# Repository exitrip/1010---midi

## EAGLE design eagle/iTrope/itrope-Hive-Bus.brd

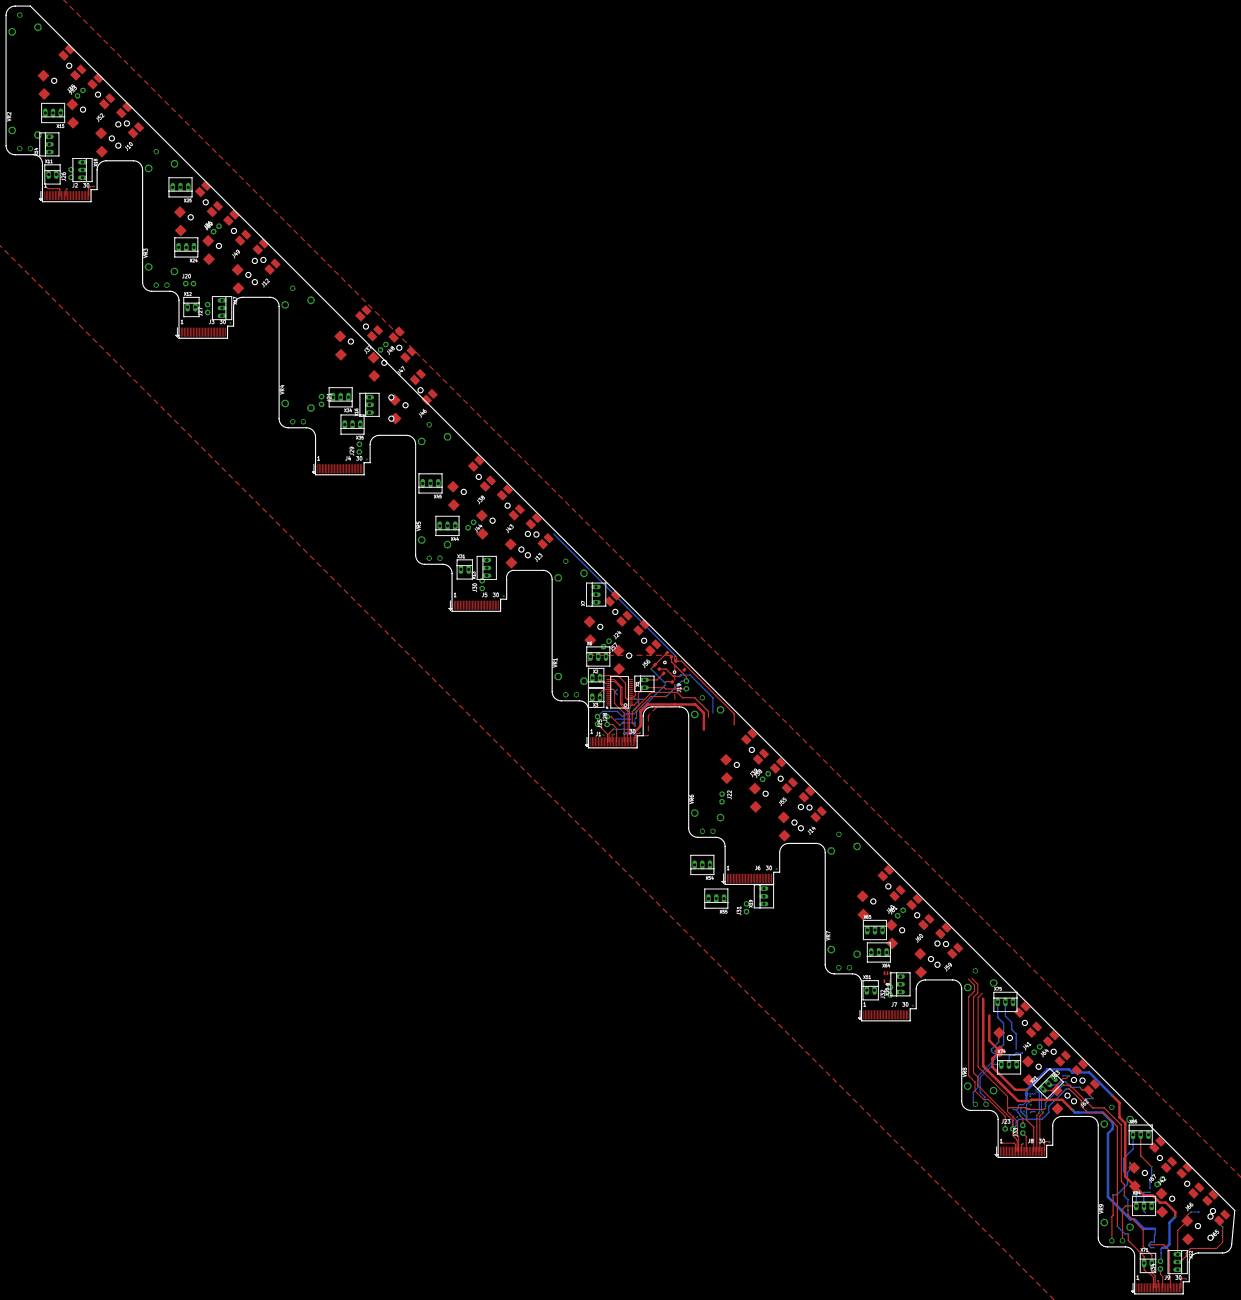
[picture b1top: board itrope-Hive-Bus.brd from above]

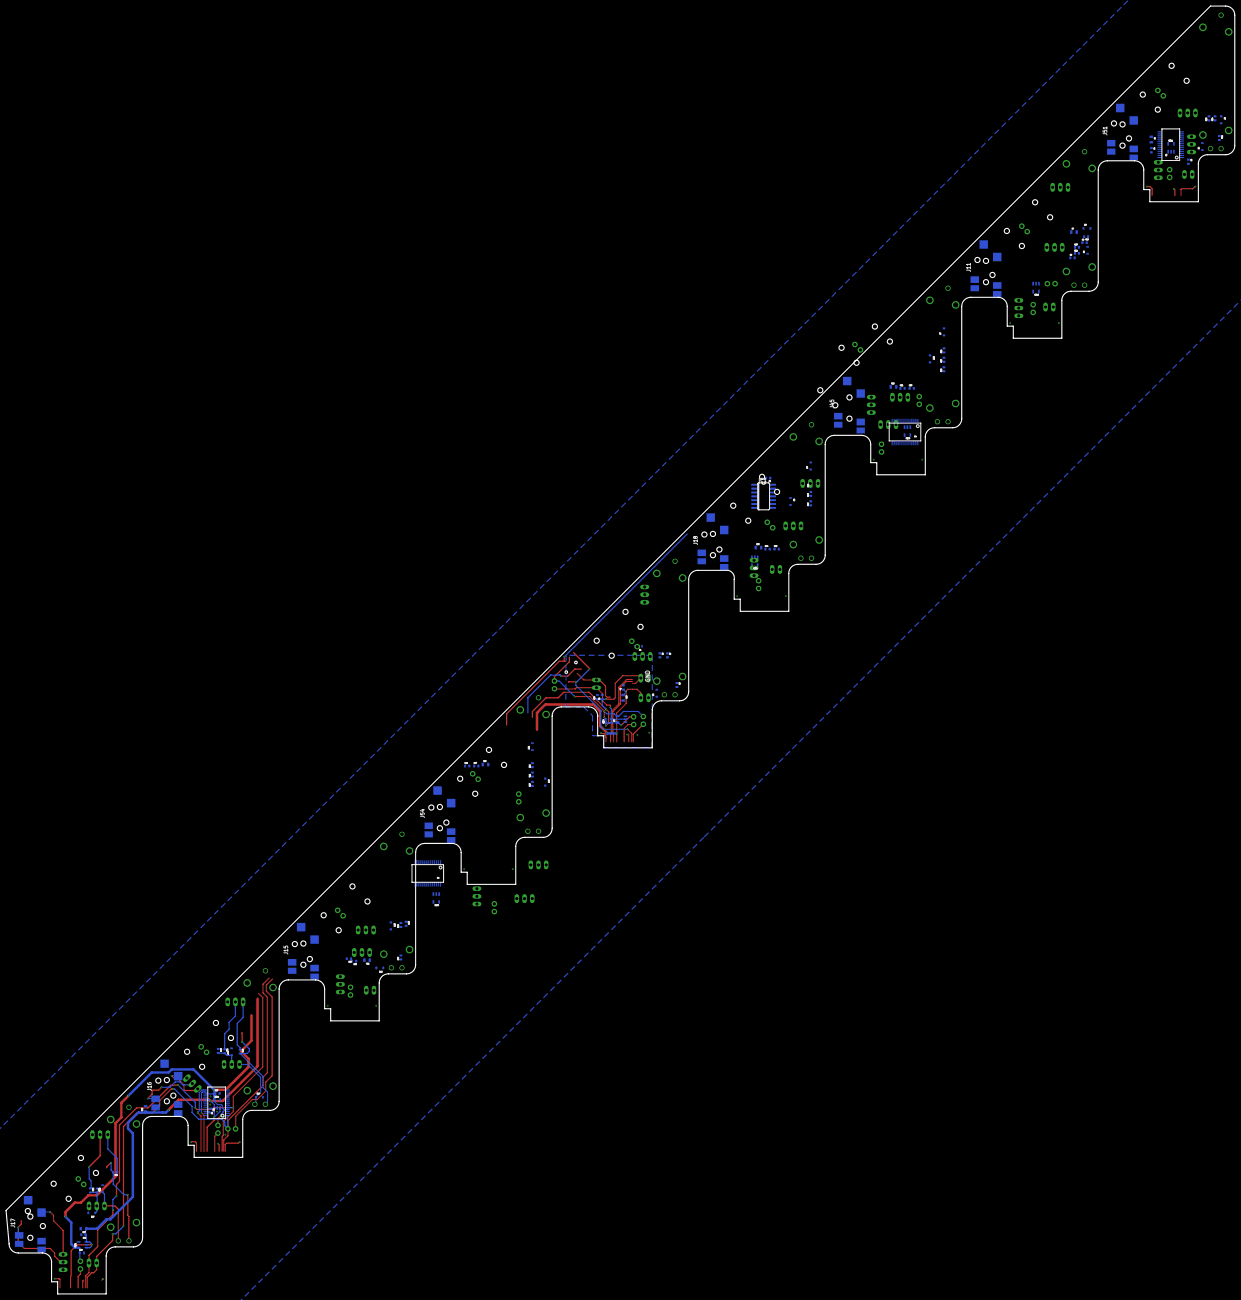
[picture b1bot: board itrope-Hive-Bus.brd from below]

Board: 2 copper layers, 405.0 x 424.5 mm, 201 parts (96 on the bottom side), 105 nets.

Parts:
C1, C2, C3, C4, C5, C8, C9, C10, C11, C13, C14, C17, C18, C19, C20, C23, C24, C25, C26, C28: 0.1uF; CAP-0603
C6, C7, C12, C15, C16, C21, C22, C27, C30: 10uF; CAP-0805
D1, D2, D3, D4, D5, D6, D7, D8, D9, D10, D11, D12, D13, D14, D15, D16, D17, D19: SOD-323
IC1: 74ALS08D; SO14
J1, J2, J3, J4, J5, J6, J7, J8, J9: ITRIP-V1; 30PINEDGE+ITRIP
J10, J11, J12, J13, J14, J15, J16, J17, J18, J24, J35, J36, J37, J38, J39, J40, J41, J42, J43, J45, J46, J47, J49, J51, J52, J54, J55, J56, J59, J60, J62, J63, J65, J66: CUI-SJ-4351
J19, J20, J21, J22, J23, J25, J26, J27, J28, J29, J30, J31, J32, J33, J34, J44, J48, J50, J53, J57, J58, J61, J64, J67: H02-PTH
R5, R7, R12, R14, R19, R21, R26, R28, R33, R35, R40, R42, R47, R49, R54, R56, R61, R63: 33k; C0402
R6, R13, R20, R27, R34, R41, R48, R55, R62: 10k; C0402
SW1: SWITCH-CK-AYZ0203
U1, U2, U4, U6, U8: FT232RL-BASICSSOP; SSOP28DB
U5: 74AHC1G125; SOT23-5
U$11, U$19, U$26, U$33, U$40, U$47, U$54, U$61: V_REG_SOT23-5_EN; SOT23-5
U$39: 74LVC1T45; SC70-6
VR1, VR2, VR3, VR4, VR5, VR6, VR7, VR8, VR9: 10K; POT-SLIDE-30MM
X1, X2, X3, X11, X12, X31, X51, X71: 22-23-2021
X6, X7, X13, X14, X15, X16, X17, X18, X19, X20, X21, X22, X24, X25, X34, X35, X44, X45, X54, X55, X64, X65, X74, X75, X84, X85: 22-23-2031

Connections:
1D+: J2.P$27, U2.15
1D-: J2.P$25, U2.16
2D+: J4.P$27, U4.15
2D-: J4.P$25, U4.16
3D+: J6.P$27, U6.15
3D-: J6.P$25, U6.16
4D+: J8.P$27, U8.15
4D-: J8.P$25, U8.16
5V: C1.1, C4.1, C6.1, C7.1, C9.1, C10.1, C12.1, C14.1, C15.1, C16.1, C18.1, C20.1, C21.1, C22.1, C24.1, C26.1, C27.1, C30.1, J1.P$23, J2.P$23, J3.P$23, J4.P$23, J5.P$23, J6.P$23, J7.P$23, J8.P$23, J9.P$23, U1.20, U2.20, U4.20, U6.20, U8.20, U$11.1, U$11.3, U$19.1, U$19.3, U$26.1, U$26.3, U$33.1, U$33.3, U$40.1, U$40.3, U$47.1, U$47.3, U$54.1, U$54.3, U$61.1, U$61.3, X3.1
+3V3: C2.1, C3.1, C5.1, C8.1, C11.1, C13.1, C17.1, C19.1, C23.1, C25.1, C28.1, IC1.14, J24.5, J25.2, J26.2, J27.2, J29.2, J30.2, J31.2, J32.2, J33.2, J34.2, J35.5, J36.5, J37.5, J38.5, J39.5, J40.5, J41.5, J42.5, U1.4, U1.17, U2.4, U2.17, U4.4, U4.17, U5.5, U6.4, U6.17, U8.4, U8.17, U$11.5, U$19.5, U$26.5, U$33.5, U$39.1, U$39.5, U$39.6, U$40.5, U$47.5, U$54.5, U$61.5, X2.1
COD+: J1.P$27, U1.15
COD-: J1.P$25, U1.16
GND: C1.2, C2.2, C3.2, C4.2, C5.2, C6.2, C7.2, C8.2, C9.2, C10.2, C11.2, C12.2, C13.2, C14.2, C15.2, C16.2, C17.2, C18.2, C19.2, C20.2, C21.2, C22.2, C23.2, C24.2, C25.2, C26.2, C27.2, C28.2, C30.2, D1.2, D2.2, D3.2, D4.2, D5.2, D6.2, D7.2, D8.2, D9.2, D10.2, D11.2, D12.2, D13.2, D14.2, D15.2, D16.2, D17.2, D19.2, IC1.7, J1.P$1, J1.P$11, J1.P$15, J1.P$16, J1.P$29, J1.P$30, J2.P$1, J2.P$11, J2.P$15, J2.P$16, J2.P$29, J2.P$30, J3.P$1, J3.P$11, J3.P$15, J3.P$16, J3.P$29, J3.P$30, J4.P$1, J4.P$11, J4.P$15, J4.P$16, J4.P$29, J4.P$30, J5.P$1, J5.P$11, J5.P$15, J5.P$16, J5.P$29, J5.P$30, J6.P$1, J6.P$11, J6.P$15, J6.P$16, J6.P$29, J6.P$30, J7.P$1, J7.P$11, J7.P$15, J7.P$16, J7.P$29, J7.P$30, J8.P$1, J8.P$11, J8.P$15, J8.P$16, J8.P$29, J8.P$30, J9.P$1, J9.P$11, J9.P$15, J9.P$16, J9.P$29, J9.P$30, J10.1, J10.4, J11.1, J11.4, J12.1, J12.4, J13.1, J13.4, J14.1, J14.4, J15.1, J15.4, J16.1, J16.4, J17.1, J17.4, J18.1, J18.4, J24.1, J24.4, J35.1, J35.4, J36.1, J36.4, J37.1, J37.4, J38.1, J38.4, J39.1, J39.4, J40.1, J40.4, J41.1, J41.4, J42.1, J42.4, J43.1, J43.4, J44.2, J45.1, J45.4, J46.1, J46.4, J47.1, J47.4, J48.2, J49.1, J49.4, J50.2, J51.1, J51.4, J52.1, J52.4, J53.2, J54.1, J54.4, J55.1, J55.4, J56.1, J56.4, J57.2, J58.2, J59.1, J59.4, J60.1, J60.4, J61.2, J62.1, J62.4, J63.1, J63.4, J64.2, J65.1, J65.4, J66.1, J66.4, J67.2, R6.1, R13.1, R20.1, R27.1, R34.1, R41.1, R48.1, R55.1, R62.1, U1.7, U1.18, U1.21, U1.25, U1.26, U2.7, U2.18, U2.21, U2.25, U2.26, U4.7, U4.18, U4.21, U4.25, U4.26, U5.1, U5.3, U6.7, U6.18, U6.21, U6.25, U6.26, U8.7, U8.18, U8.21, U8.25, U8.26, U$11.2, U$19.2, U$26.2, U$33.2, U$39.2, U$40.2, U$47.2, U$54.2, U$61.2, VR1.3, VR1.P$4, VR1.P$5, VR1.P$6, VR1.P$7, VR2.3, VR2.P$4, VR2.P$5, VR2.P$6, VR2.P$7, VR3.3, VR3.P$4, VR3.P$5, VR3.P$6, VR3.P$7, VR4.3, VR4.P$4, VR4.P$5, VR4.P$6, VR4.P$7, VR5.3, VR5.P$4, VR5.P$5, VR5.P$6, VR5.P$7, VR6.3, VR6.P$4, VR6.P$5, VR6.P$6, VR6.P$7, VR7.3, VR7.P$4, VR7.P$5, VR7.P$6, VR7.P$7, VR8.3, VR8.P$4, VR8.P$5, VR8.P$6, VR8.P$7, VR9.3, VR9.P$4, VR9.P$5, VR9.P$6, VR9.P$7, X2.2, X3.2, X6.3, X7.3, X13.3, X14.3, X15.3, X16.3, X17.3, X18.3, X19.3, X20.3, X21.3, X22.3, X24.3, X25.3, X34.3, X35.3, X44.3, X45.3, X54.3, X55.3, X64.3, X65.3, X74.3, X75.3, X84.3, X85.3
LCV1-1: D4.1, VR2.2, X14.1
LCV1-2: D6.1, VR3.2, X24.1
LCV1-3: D19.1, VR4.2, X34.1
LCV1-4: D8.1, VR5.2, X44.1
LCV1-5: D10.1, VR6.2, X54.1
LCV1-6: D12.1, VR7.2, X64.1
LCV1-7: D14.1, VR8.2, X74.1
LCV1-8: D16.1, VR9.2, X84.1
LCV1-CO: D2.1, VR1.2, X6.1
LCV2-1: D3.1, R13.2, R14.2, X14.2
LCV2-2: D5.1, R20.2, R21.2, X24.2
LCV2-3: D7.1, R27.2, R28.2, X34.2
LCV2-4: D9.1, R34.2, R35.2, X44.2
LCV2-5: D11.1, R41.2, R42.2, X54.2
LCV2-6: D13.1, R48.2, R49.2, X64.2
LCV2-7: D15.1, R55.2, R56.2, X74.2
LCV2-8: D17.1, R62.2, R63.2, X84.2
LCV2-CO: D1.1, R6.2, R7.2, X6.2
unnamed: R7.1, X7.2
unnamed: R5.1, X7.1
unnamed: J1.P$18, J25.1
unnamed: R14.1, X15.2
unnamed: R12.1, X15.1
unnamed: J24.2, R5.2, VR1.1
unnamed: J2.P$18, J26.1
unnamed: J3.P$18, J27.1
unnamed: R21.1, X25.2
unnamed: R19.1, X25.1
unnamed: J4.P$18, J29.1
unnamed: R28.1, X35.2
unnamed: R26.1, X35.1
unnamed: J5.P$18, J30.1
unnamed: J6.P$18, J31.1
unnamed: J7.P$18, J32.1
unnamed: R35.1, X45.2
unnamed: R33.1, X45.1
unnamed: J8.P$18, J33.1
unnamed: R42.1, X55.2
unnamed: R40.1, X55.1
unnamed: IC1.6, IC1.12
unnamed: IC1.3, IC1.13
unnamed: J1.P$12, J28.2
unnamed: R49.1, X65.2
unnamed: R47.1, X65.1
unnamed: J9.P$18, J34.1
unnamed: R56.1, X75.2
unnamed: R54.1, X75.1
unnamed: J35.2, R12.2, VR2.1
unnamed: J36.2, R19.2, VR3.1
unnamed: J37.2, R26.2, VR4.1
unnamed: R63.1, X85.2
unnamed: R61.1, X85.1
unnamed: J38.2, R33.2, VR5.1
unnamed: J39.2, R40.2, VR6.1
unnamed: J40.2, R47.2, VR7.1
unnamed: J41.2, R54.2, VR8.1
unnamed: J42.2, R61.2, VR9.1
unnamed: J13.2, J18.2, X13.1
unnamed: J13.3, J18.3, X13.2
unnamed: J43.2, J44.1
unnamed: J45.2, J46.2, X16.1
unnamed: J45.3, J46.3, X16.2
unnamed: J47.2, J48.1
unnamed: J11.2, J12.2, X17.1
unnamed: J11.3, J12.3, X17.2
unnamed: J49.2, J50.1
unnamed: J10.2, J51.2, X18.1
unnamed: J10.3, J51.3, X18.2
unnamed: J52.2, J53.1
unnamed: J14.2, J54.2, X19.1
unnamed: J14.3, J54.3, X19.2
unnamed: J56.2, J57.1
unnamed: J55.2, J58.1
unnamed: J15.2, J59.2, X20.1
unnamed: J15.3, J59.3, X20.2
unnamed: J60.2, J61.1
unnamed: J16.2, J62.2, X21.1
unnamed: J16.3, J62.3, X21.2
unnamed: J63.2, J64.1
unnamed: J17.2, J65.2, X22.1
unnamed: J17.3, J65.3, X22.2
unnamed: J66.2, J67.1
RXD: J2.P$13, J3.P$13, J4.P$13, J5.P$13, J6.P$13, J7.P$13, J8.P$13, J9.P$13, SW1.C1, U2.5, U4.5, U6.5, U8.5, X11.2, X12.2, X31.2, X51.2, X71.2
RXUSB: SW1.C2, U1.5, X1.2
TXBUS: IC1.11, J20.1, J21.1, J22.1, J23.1, SW1.5
TXCO: J1.P$13, SW1.1, SW1.4, SW1.6
TXD1: IC1.4, J2.P$12, J3.P$12, J20.2, U2.1, X11.1, X12.1
TXD2: IC1.5, J4.P$12, J5.P$12, J21.2, U4.1, X31.1
TXD3: IC1.1, J6.P$12, J7.P$12, J22.2, U6.1, X51.1
TXD4: IC1.2, J8.P$12, J9.P$12, J23.2, U8.1, X71.1
TXUSB: J19.2, J28.1, SW1.2, U5.4, U$39.4
TXUSB_FTDI: J19.1, U1.1, U5.2, U$39.3, X1.1
